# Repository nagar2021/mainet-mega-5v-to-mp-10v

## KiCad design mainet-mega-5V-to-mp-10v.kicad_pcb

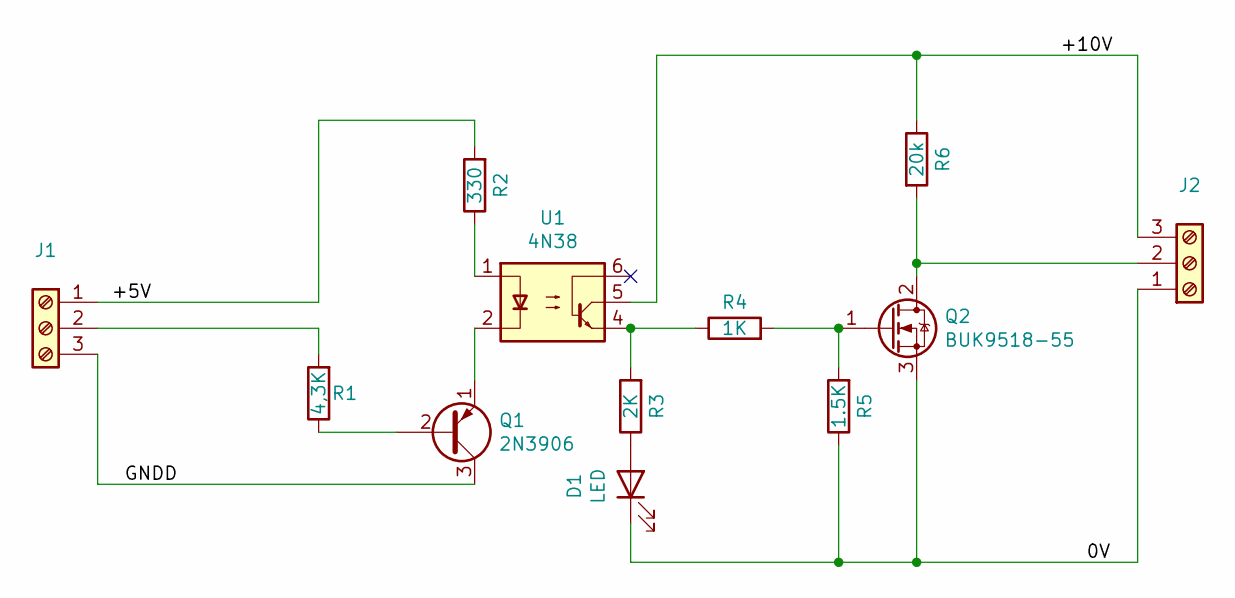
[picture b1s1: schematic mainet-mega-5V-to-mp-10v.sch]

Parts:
D1: LED; LED_D5.0mm
J1, J2: Screw_Terminal_01x03; Altech_AK300_1x03_P5.00mm_45-Degree
Q1: 2N3906; TO-92_Inline
Q2: BUK9518-55; TO-220-3_Vertical
R1: 4,3K; R_Axial_DIN0207_L6.3mm_D2.5mm_P7.62mm_Horizontal
R2: 330; R_Axial_DIN0207_L6.3mm_D2.5mm_P7.62mm_Horizontal
R3: 2K; R_Axial_DIN0207_L6.3mm_D2.5mm_P7.62mm_Horizontal
R4: 1K; R_Axial_DIN0207_L6.3mm_D2.5mm_P7.62mm_Horizontal
R5: 1.5K; R_Axial_DIN0207_L6.3mm_D2.5mm_P7.62mm_Horizontal
R6: 20k; R_Axial_DIN0207_L6.3mm_D2.5mm_P7.62mm_Horizontal
U1: 4N38; DIP-6_W7.62mm

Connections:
/0V: D1.1 (K), J2.1, Q2.3 (S), R5.1
/+5V: J1.1, R2.2
/+10V: J2.3, R6.1, U1.5
/GNDD: J1.3, Q1.3 (C)
unnamed: D1.2 (A), R3.1
unnamed: J1.2, R1.2
unnamed: J2.2, Q2.2 (D), R6.2
unnamed: Q1.1 (E), U1.2
unnamed: Q1.2 (B), R1.1
unnamed: Q2.1 (G), R4.2, R5.2
unnamed: R2.1, U1.1
unnamed: R3.2, R4.1, U1.4

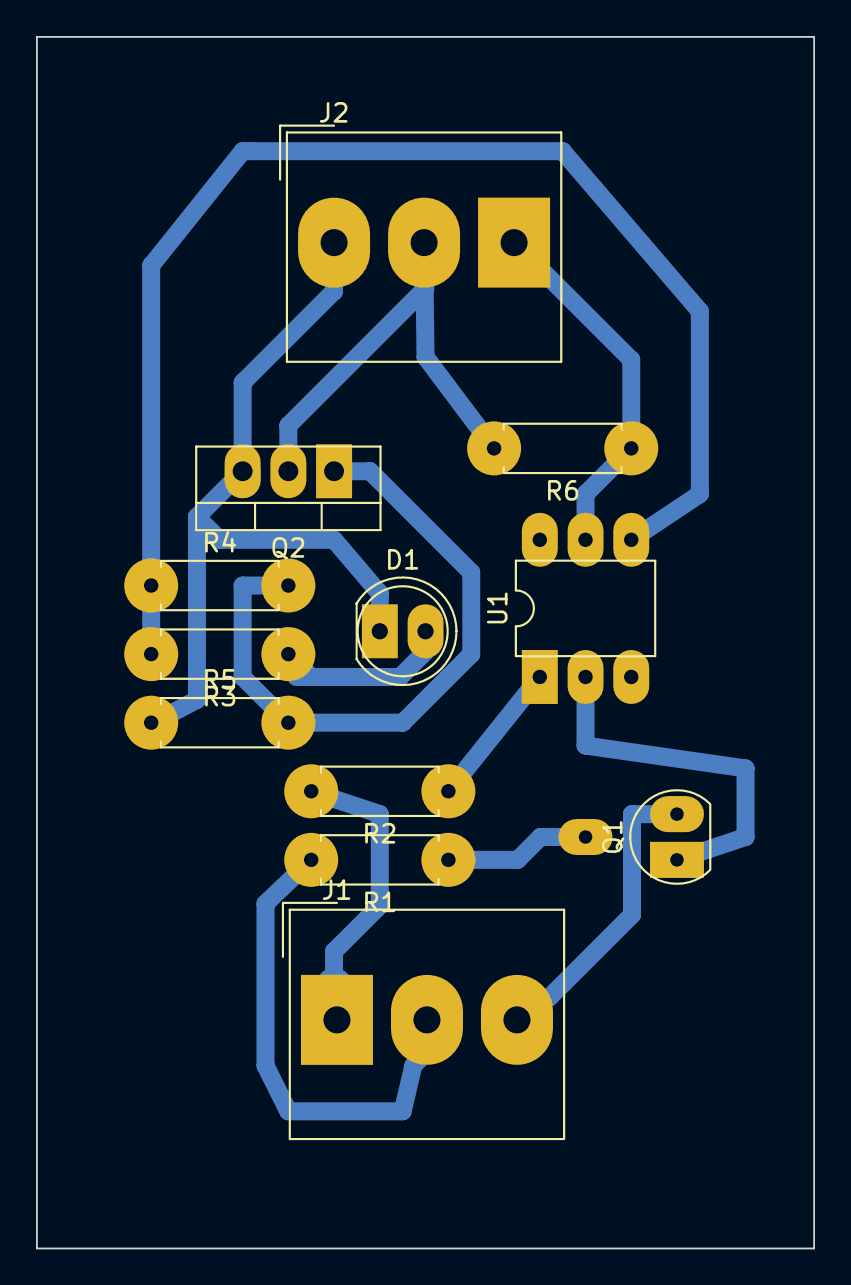
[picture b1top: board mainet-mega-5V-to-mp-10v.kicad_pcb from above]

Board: 2 copper layers, 43.2 x 67.3 mm, 12 parts (0 on the bottom side), 12 nets.

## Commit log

2021-03-09 Confirmación inicial
2021-03-09 PCB V0.1
2021-03-09 Correción de pistas
2021-03-10 Agregar título al esquemático... del convertidor de voltaje Mainet-mega-5V a MP-10V
2021-03-15 KICAD: Modificar PCB: 5v-to-mp-10v
2021-03-15 KICAD: Modificar PCB mainet-mega-5v-to-mp-10v
2021-03-15 KICAD: Agregar pdf mainet-mega-5v-to-mp-10v
2021-03-15 KICAD: Agregar pdf/mainet-mega-5v-to-10v
